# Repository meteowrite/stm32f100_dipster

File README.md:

# Yet another STM32F100 Board

Simple board to ease the work with STM32F100 LQFP64 devices that I have laying around.
Pitch between SIL headers is multiple of 2.54, making it suitable for breadboarding as well. 

# Features

- Reset Push button
- Boot configuration (Flash/System ROM) DIP switch 
- PD2 routed to DIP switch as well
- XTAL provision
- Hardwired USART1 and SWD headers
- Mounting holes
- Minimalistic patch/prototype area (visible as pin headers in the 3D)

# What is missing

- No LED indicator, not even for power indication

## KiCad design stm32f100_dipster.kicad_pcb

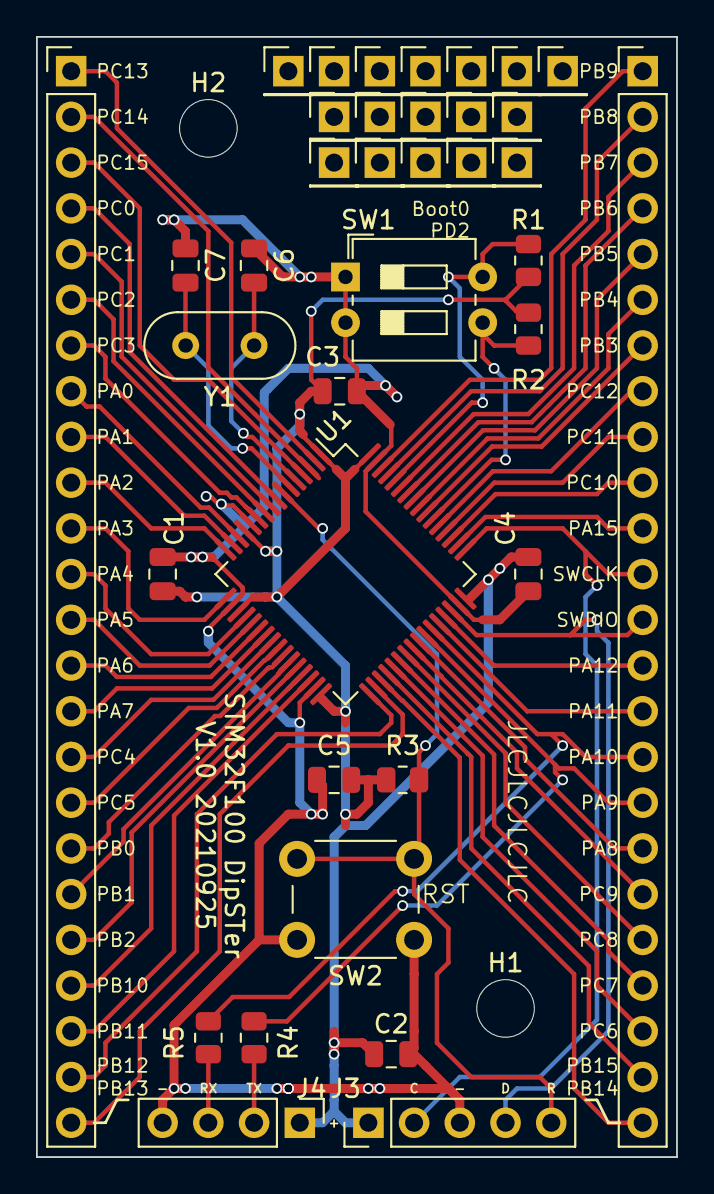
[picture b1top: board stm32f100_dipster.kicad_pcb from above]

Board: 2 copper layers, 35.6 x 62.2 mm, 22 parts (0 on the bottom side), 57 nets.

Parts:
C1, C2, C3, C4, C5, C6, C7: 100n; C_0805_2012Metric
H1, H2: MountingHole; MountingHole_3.2mm_M3
J1, J2: Conn_01x24; PinHeader_1x24_P2.54mm_Vertical
J3: Conn_01x05; PinHeader_1x05_P2.54mm_Vertical
J4: Conn_01x04; PinHeader_1x04_P2.54mm_Vertical
R1, R2, R3, R4, R5: 4.7k; R_0805_2012Metric
SW1: SW_DIP_x02; SW_DIP_SPSTx02_Slide_6.7x6.64mm_W7.62mm_P2.54mm_LowProfile
SW2: SW_Push; SW_PUSH_6mm
U1: STM32F100R6Tx; LQFP-64_10x10mm_P0.5mm
Y1: Crystal; Crystal_HC52-6mm_Vertical

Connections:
+3V3: C1.1, C2.1, C3.1, C4.1, C5.1, J3.1, J4.1, R1.1, R2.1, R3.1, U1.1, U1.13, U1.19, U1.32, U1.48, U1.64
/BOOT0: R1.2, SW1.4, U1.60
/NRST: J3.5, R3.2, SW2.2, U1.7
/OSC_IN: C6.2, U1.5, Y1.1
/OSC_OUT: C7.2, U1.6, Y1.2
/PA0: J1.8, U1.14
/PA1: J1.9, U1.15
/PA2: J1.10, U1.16
/PA3: J1.11, U1.17
/PA4: J1.12, U1.20
/PA5: J1.13, U1.21
/PA6: J1.14, U1.22
/PA7: J1.15, U1.23
/PA8: J2.18, U1.41
/PA9: J2.17, R4.2, U1.42
/PA10: J2.16, R5.2, U1.43
/PA11: J2.15, U1.44
/PA12: J2.14, U1.45
/PA15: J2.11, U1.50
/PB0: J1.18, U1.26
/PB1: J1.19, U1.27
/PB2: J1.20, U1.28
/PB3: J2.7, U1.55
/PB4: J2.6, U1.56
/PB5: J2.5, U1.57
/PB6: J2.4, U1.58
/PB7: J2.3, U1.59
/PB8: J2.2, U1.61
/PB9: J2.1, U1.62
/PB10: J1.21, U1.29
/PB11: J1.22, U1.30
/PB12: J1.23, U1.33
/PB13: J1.24, U1.34
/PB14: J2.24, U1.35
/PB15: J2.23, U1.36
/PC0: J1.4, U1.8
/PC1: J1.5, U1.9
/PC2: J1.6, U1.10
/PC3: J1.7, U1.11
/PC4: J1.16, U1.24
/PC5: J1.17, U1.25
/PC6: J2.22, U1.37
/PC7: J2.21, U1.38
/PC8: J2.20, U1.39
/PC9: J2.19, U1.40
/PC10: J2.10, U1.51
/PC11: J2.9, U1.52
/PC12: J2.8, U1.53
/PC13: J1.1, U1.2
/PC14: J1.2, U1.3
/PC15: J1.3, U1.4
/PD2: R2.2, SW1.3, U1.54
/SWCLK: J2.12, J3.2, U1.49
/SWDIO: J2.13, J3.4, U1.46
/USART1_RX: J4.3, R5.1
/USART1_TX: J4.2, R4.1
GND: C1.2, C2.2, C3.2, C4.2, C5.2, C6.1, C7.1, J3.3, J4.4, SW1.1, SW1.2, SW2.1, U1.12, U1.18, U1.31, U1.47, U1.63

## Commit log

2021-09-25 Create README.md
    initial commit
2021-09-25 Adding KiCAD files and Gerber zip
2021-09-25 adding schematic and PCB images
2021-09-25 Readme update
